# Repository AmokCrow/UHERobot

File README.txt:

This repo is for the Under House Explorer robot project.

Contents:
RobotControlBoard - Code for the MCU on the robot's PCB.
RobotControlDaemon - an FCGI server process. Mediates between the web UI and the control board serial port.
StaticWebContent - The web UI.

Library dependencies:
libpthreads-dev (may be called libevent-pthreads in your distro now)
libfcgi-dev (basic FastCGI interface, get c++ ver if separate)
libpthreads-dev (needed for fcgi's threading)
libcgicc-dev (does the cgi inputs parsing)
spawn-fcgi (a lighttdp spin-off, a magic tool for spawning and un-parenting an fgci process with the right pipe. Don't ask me how it does it.)

Usage:
1. Install the cross-compilation toolchain for your Linux board. (You don't want to compile on a low-power single-board computer, trust me.)
  - For the Arietta board, see acmesystems.it . They made it and provide fairly good instructions for the toolchain.
  - For Raspberry Pi... google "cross-compile Qt for Raspberry Pi".
2. Boot your Linux board. The one that you're going to use as the robot's brains.
3. On your Linux board, install the above libraries, plus Nginx server.
4. Uninstall Apache, unless you know better and/or actually use Apache for something. If it's installed in the first place. Arietta came with Apache installed.
5. Shut down your Linux board. Take out the memory card. Use the "dd" command to copy the card contents into an image on your hard drive.

For Arietta:
6. Mount the larger partition in the image to /mnt/ariettaroot
  - You can get the partitions in the image with the command "fdisk -l <image-file-name>"
  - You then mount with "mount -o loop,offset=<filesystem-offset-in-bytes> <image-file-name> /mnt/ariettaroot
  - You can mount elsewhere, but then you'll have to fix the path to the root filesystem in arietta.cmake
7. Make a directory named "build-daemon". Navigate in it.
8. Copy the arietta.cmake file into this directory.
9. Call cmake with "cmake -DCMAKE_TOOLCHAIN_FILE=arietta.cmake ../RobotControlDaemon"
  - If it complains about not finding referenced items, it means that the Linux board image is missing some of the dependency libraries. Or is not mounted correctly.
10. Call "make"

For Raspberry Pi:
6. Cross-compile Qt. (I had this done. I write what I know.)
7. Install Qt on the Raspberry Pi image.
8. Notice that the qmake executable is actually still built for your PC even though the rest of it is cross-compiled.
9. Navigate to the folder RobotControlDaemon
10. Call the cross-compile qmake
11. Call "make"

Common for both:
12. Copy the image back to the memory card, insert to your Linux board and boot it up.
13. Copy the cross-compiled executable to your board.

For Arietta:
14. Using the online tools at acmesystems.it, make a pin configuration file that will give you a UART.
  - Get the UART on pins that match the custom PCB if mounting it directly on top.
15. Download the configuration file to the Arietta board's boot partition.
16. Replace the previous configuration file there.
17. Reboot the board for the new configuration to take effect.

For Raspberry Pi:
14. Disable the shell in the serial port.
  - On newer images, this is one of the first-bot configuration options.
  - For older images, follow Adafruit's instructions on the subject.

Common for both:
18. Copy the scripts in daemon_build_scripts/target_run_scripts to the Linux board, to folder /home/pi/RCD
19. Copy the folder StaticWebContent to the Linux board to /home/pi/RCD/StaticWebContent
20. Copy the cross-compiled executable to /home/pi/RDC/bin
21. Make /home/pi/RCD/install_config.sh executable and execute it. This should copy the nginx config in the right place.
22. Make similarly executable and execute the install_daemon.sh script. This should get the cross-compiled executable to be handled as a daemon.
23. Check that the UART port name in start_daemon.sh is correct.
24. Make start_daemon.sh and kill_daemon.sh executable if they are not already.
25. Reboot the Linux board.
26. Done. Finished. ...Profit?
  - The Linux board should have the nginx server running and serving the robot's UI.
  - For an easier life, consider setting a static address for the robot. See /etc/networking/interfaces.conf and google "Linux interfaces static address".

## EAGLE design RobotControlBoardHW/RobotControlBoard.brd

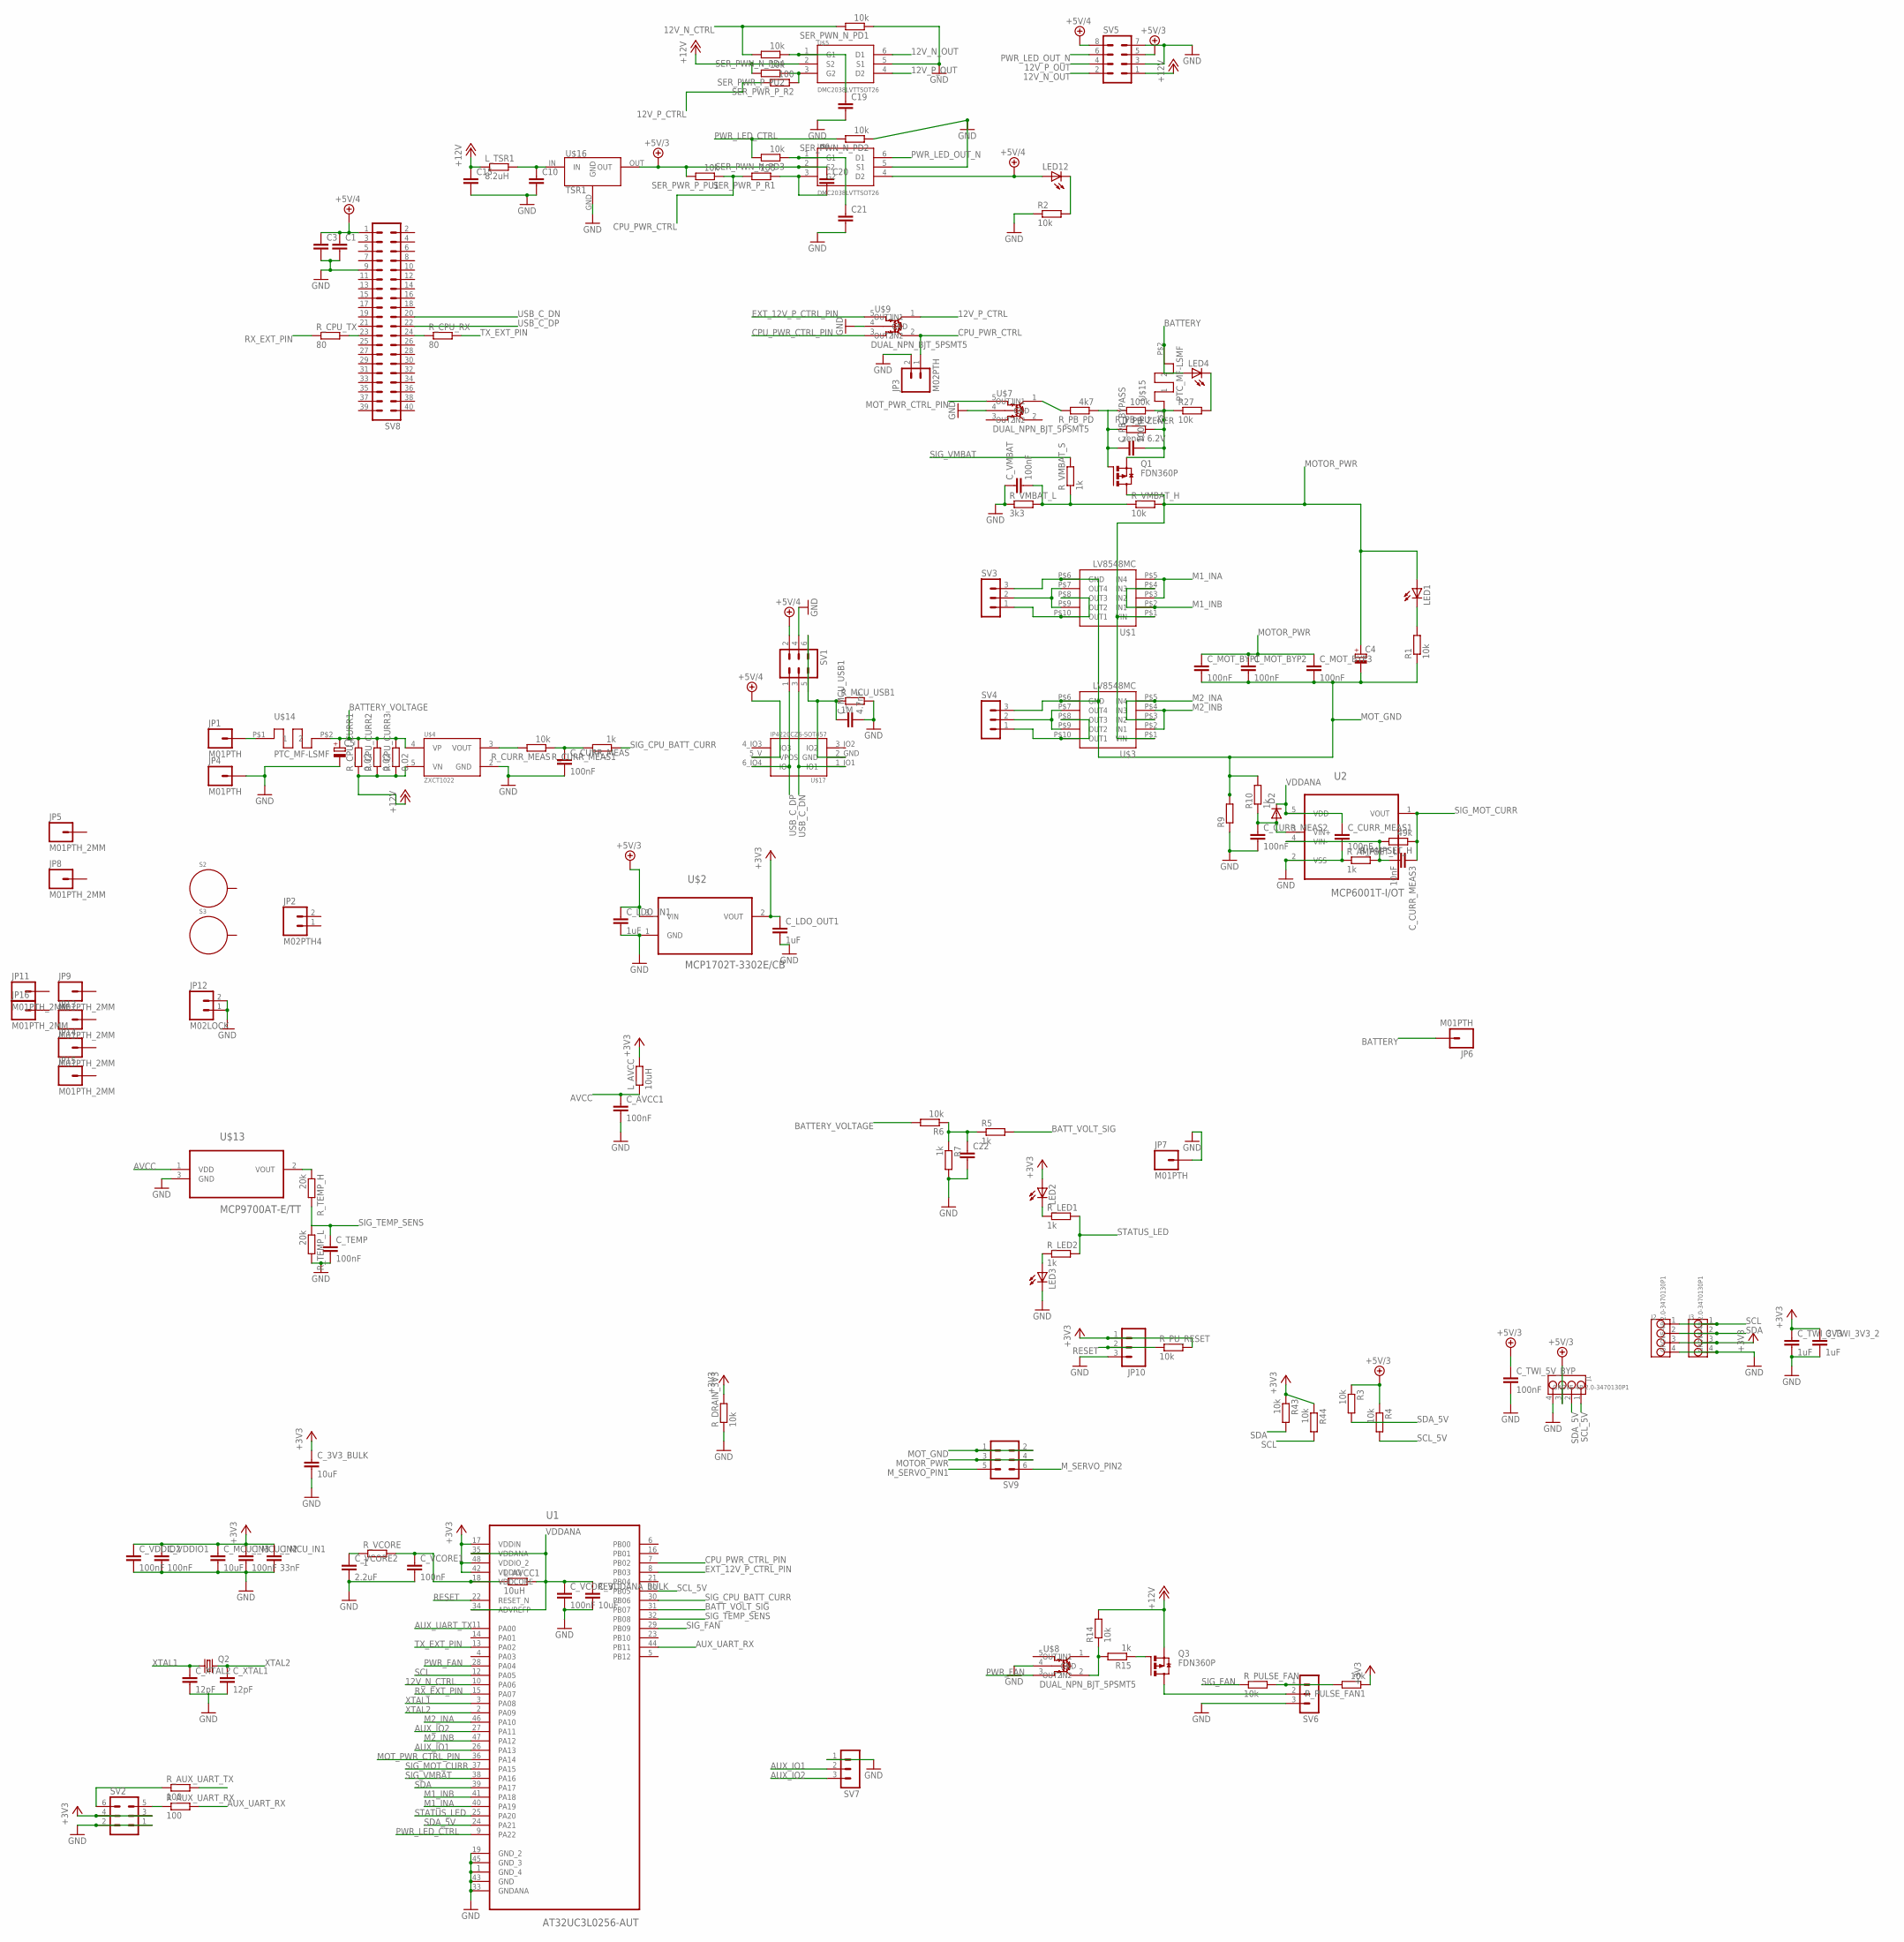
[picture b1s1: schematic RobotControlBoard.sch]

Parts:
C1, C3: C-EUC1210K; C1210K
C4: CPOL-EUE3.5-8; E3,5-8
C5: CPOL-EUE2.5-6; E2,5-6
C10, C15: C-EUC0805; C0805
C19, C20, C21, C22: C-EUC0603K; C0603K
C_3V3_BULK: 10uF; C1206
C_AVCC1: 100nF; C0603
C_CURR_MEAS, C_CURR_MEAS1, C_CURR_MEAS2: 100nF; C0603K
C_CURR_MEAS3: 10nF; C0603K
C_LDO_IN1: 1uF; C0805
C_LDO_OUT1: 1uF; C0805
C_MCU_IN1: 33nF; C0603K
C_MCU_IN2: 100nF; C0603K
C_MCU_IN3: 10uF; C0805
C_MCU_USB1: 4.7nF; C0603
C_MOT_BYP1, C_MOT_BYP2, C_MOT_BYP3: 100nF; C0603K
C_PB_BYPASS: 100nF; C0603K
C_TEMP: 100nF; C0603
C_TWI_3V3, C_TWI_3V3_2: 1uF; C0805K
C_TWI_5V_BYP: 100nF; C0603K
C_VCORE1, C_VCORE3: 100nF; C0603K
C_VCORE2: 2.2uF; C0805
C_VDDANA_BULK: 10uF; C0805
C_VDDIO1, C_VDDIO2: 100nF; C0603K
C_VMBAT: 100nF; C0603K
C_XTAL1, C_XTAL2: 12pF; C0603K
D2: DIODE-SOD323-W; SOD323-W
D_PB_ZENER: zener 6.2V; R0805W
J1, J2, J3: GROVE-4P-2.0-3470130P1; 4P-2.0
JP1, JP4, JP6, JP7: M01PTH; 1X01
JP2: M02PTH4; 1X02_XTRA_BIG
JP3: M02PTH; 1X02
JP5, JP8, JP9, JP11, JP13, JP14, JP15, JP16: M01PTH_2MM; 1X01_2MM
JP10: M03PTH; 1X03
JP12: M02LOCK; 1X02_LOCK
LED1, LED2, LED3, LED4, LED12: LEDSML0603; SML0603
L_AVCC: 10uH; R0603
L_AVCC1: 10uH; R0805
L_TSR1: 8.2uH; M0805
Q1, Q3: FDN360P; SUPER-SOT3
Q2: CRYSTALHC49S; HC49/S
R1, R2, R3, R4, R6, R14, R27, R43, R44: 10k; R0603
R5, R7, R10, R15: 1k; R0603
R9: R-EU_M1206; M1206
R_AMPSET_H: 49k; R0603
R_AMPSET_L: 1k; R0603
R_AUX_UART_RX: 100; R0603
R_AUX_UART_TX: 100; R0603
R_CPU_CURR1, R_CPU_CURR2, R_CPU_CURR3: 0.02; R0805
R_CPU_RX: 80; R0603
R_CPU_TX: 80; R0603
R_CURR_MEAS: 10k; R0603
R_CURR_MEAS1: 1k; R0603
R_DRAIN_3V3: 10k; R0603
R_LED1, R_LED2: 1k; R0603
R_MCU_USB1: 1M; R0603
R_PB_PD: 4k7; R0603
R_PB_PU: 100k; R0603
R_PULSE_FAN, R_PULSE_FAN1: 10k; R0603
R_PU_RESET: 10k; R0603
R_TEMP_H: 20k; R0603
R_TEMP_L: 20k; R0603
R_VCORE: 1; R0603
R_VMBAT_H: 10k; R0603
R_VMBAT_L: 3k3; R0603
R_VMBAT_S: 1k; R0603
S2, S3: STANDOFF_ELECTRICAL; STANDOFF-ELECTRICAL
SER_PWN_N_PD1, SER_PWN_N_PD2, SER_PWN_N_PD3, SER_PWN_N_PD4: 10k; R0603
SER_PWR_P_PU1, SER_PWR_P_PU2: 10k; R0603
SER_PWR_P_R1, SER_PWR_P_R2: 100; R0603
SV1, SV2, SV9: MA03-2
SV3, SV4, SV6, SV7: MA03-1
SV5: MA04-2
SV8: MA20-2
U1: AT32UC3L0256-AUT; QFP50P900X900X120-48N
U2: MCP6001T-I/OT; SOT95P270X145-5N
U$1, U$3: LV8548MC; SOIC10
U$2: MCP1702T-3302E/CB; SOT95P255X145-3N
U$4: ZXCT1022; SOT23-5
U$5, U$6: DMC2038LVTTSOT26; TSOT26
U$7, U$8, U$9: DUAL_NPN_BJT_5PSMT5; SC-74A
U$13: MCP9700AT-E/TT; SOT95P237X112-3N
U$14, U$15: PTC_MF-LSMF; PTC_FUSE_BOURNS
U$16: TSR1; TSR-1
U$17: IP4220CZ6-SOT457; SOT457_NXP_ESD

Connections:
12V_N_CTRL: SER_PWN_N_PD1.2, SER_PWN_N_PD4.2, U1.10 (PA06)
12V_N_OUT: SV5.2, U$5.6 (D1)
12V_P_CTRL: SER_PWR_P_R2.2, U$9.1 (OUT1)
12V_P_OUT: SV5.4, U$5.4 (D2)
+3V3: C_3V3_BULK.1, C_LDO_OUT1.1, C_MCU_IN1.1, C_MCU_IN2.1, C_MCU_IN3.1, C_TWI_3V3.1, C_TWI_3V3_2.1, C_VDDIO1.1, C_VDDIO2.1, J2.3, J3.3, JP10.1, LED2.A, L_AVCC.2, R43.1, R44.1, R_DRAIN_3V3.2, R_PULSE_FAN1.1, R_PU_RESET.2, SV2.3, SV2.4, U1.17 (VDDIN), U1.42 (VDDIO), U1.48 (VDDIO_2), U$2.2 (VOUT)
+5V/3: C20.1, C_LDO_IN1.1, C_TWI_5V_BYP.1, J1.3, R3.1, R4.1, SER_PWR_P_PU1.2, SV5.5, U$2.3 (VIN), U$6.2 (S2), U$16.OUT
+5V/4: C1.1, C3.1, LED12.A, SV1.2, SV5.8, SV8.1, U$6.4 (D2), U$17.5_V (VPOS)
+12V: C15.1, L_TSR1.1, Q3.2 (S), R14.2, R_CPU_CURR1.1, R_CPU_CURR2.1, R_CPU_CURR3.1, SER_PWR_P_PU2.2, SV5.1, U$4.5 (VN), U$5.2 (S2)
AUX_IO1: SV7.2, U1.26 (PA13)
AUX_IO2: SV7.3, U1.27 (PA11)
AUX_UART_RX: R_AUX_UART_RX.2, U1.44 (PB11)
AUX_UART_TX: R_AUX_UART_TX.2, U1.11 (PA00)
AVCC: C_AVCC1.1, L_AVCC.1, U$13.1 (VDD)
BATTERY: JP6.1, LED4.A, U$15.P$2 (2)
BATTERY_VOLTAGE: C5.+, R6.2, R_CPU_CURR1.2, R_CPU_CURR2.2, R_CPU_CURR3.2, U$4.4 (VP), U$14.P$2 (2)
BATT_VOLT_SIG: R5.2, U1.31 (PB07)
BATT_VOLT_SIG_N: C22.1, R5.1, R6.1, R7.1
CPU_PWR_CTRL: JP3.1, SER_PWR_P_PU1.1, SER_PWR_P_R1.2, U$9.2 (OUT2)
CPU_PWR_CTRL_PIN: U1.7 (PB02), U$9.3 (IN2)
EXT_12V_P_CTRL_PIN: U1.8 (PB03), U$9.5 (IN1)
GND: C1.2, C3.2, C5.-, C10.2, C15.2, C19.2, C21.2, C22.2, C_3V3_BULK.2, C_AVCC1.2, C_CURR_MEAS.2, C_CURR_MEAS1.2, C_CURR_MEAS2.2, C_LDO_IN1.2, C_LDO_OUT1.2, C_MCU_IN1.2, C_MCU_IN2.2, C_MCU_IN3.2, C_MCU_USB1.2, C_TEMP.2, C_TWI_3V3.2, C_TWI_3V3_2.2, C_TWI_5V_BYP.2, C_VCORE1.2, C_VCORE2.2, C_VCORE3.2, C_VDDANA_BULK.2, C_VDDIO1.2, C_VDDIO2.2, C_VMBAT.1, C_XTAL1.2, C_XTAL2.2, J1.4, J2.4, J3.4, JP3.2, JP4.1, JP7.1, JP10.3, JP12.1, JP12.2, LED3.C, R2.1, R7.2, R9.1, R_AMPSET_L.1, R_DRAIN_3V3.1, R_MCU_USB1.2, R_TEMP_L.2, R_VMBAT_L.1, SER_PWN_N_PD1.1, SER_PWN_N_PD2.1, SV1.4, SV2.1, SV2.2, SV5.3, SV5.7, SV6.3, SV7.1, SV8.9, U1.1 (GND_4), U1.19 (GND_2), U1.33 (GNDANA), U1.43 (GND), U1.45 (GND_3), U2.2 (VSS), U$2.1 (GND), U$4.2 (GND), U$5.5 (S1), U$6.5 (S1), U$7.4 (GND), U$8.4 (GND), U$9.4 (GND), U$13.3 (GND), U$16.GND
M1_INA: U1.40 (PA19), U$1.P$3 (IN2), U$1.P$5 (IN4)
M1_INB: U1.41 (PA18), U$1.P$2 (IN1), U$1.P$4 (IN3)
M2_INA: U1.46 (PA10), U$3.P$3 (IN2), U$3.P$5 (IN4)
M2_INB: U1.47 (PA12), U$3.P$2 (IN1), U$3.P$4 (IN3)
MOTOR_PWR: C4.+, C_MOT_BYP1.1, C_MOT_BYP2.1, C_MOT_BYP3.1, LED1.A, Q1.3 (D), R_VMBAT_H.2, SV9.3, SV9.4, U$1.P$1 (VIN), U$3.P$1 (VIN)
MOT_GND: C4.-, C_MOT_BYP1.2, C_MOT_BYP2.2, C_MOT_BYP3.2, R1.1, R9.2, R10.2, SV3.3, SV4.3, SV9.1, SV9.2, U$1.P$6 (GND), U$3.P$6 (GND)
MOT_PWR_CTRL_PIN: U1.36 (PA14), U$7.5 (IN1)
M_SERVO_PIN1: SV9.5
M_SERVO_PIN2: SV9.6
unnamed: R_AUX_UART_RX.1, SV2.5
unnamed: LED3.A, R_LED2.1
unnamed: LED2.C, R_LED1.1
unnamed: R_CURR_MEAS.2, U$4.3 (VOUT)
unnamed: C_VMBAT.2, R_VMBAT_H.1, R_VMBAT_L.2, R_VMBAT_S.1
unnamed: JP1.1, U$14.P$1 (1)
unnamed: C_VCORE2.1, R_VCORE.1
unnamed: C20.2, SER_PWR_P_R1.1, U$6.3 (G2)
unnamed: SV3.1, U$1.P$8 (OUT3), U$1.P$10 (OUT1)
unnamed: C19.1, SER_PWN_N_PD4.1, U$5.1 (G1)
unnamed: SV3.2, U$1.P$7 (OUT4), U$1.P$9 (OUT2)
unnamed: C_PB_BYPASS.2, D_PB_ZENER.2, Q1.2 (S), R27.1, R_PB_PU.1, U$15.P$1 (1)
unnamed: SER_PWR_P_PU2.1, SER_PWR_P_R2.1, U$5.3 (G2)
unnamed: R_AUX_UART_TX.1, SV2.6
unnamed: C_PB_BYPASS.1, D_PB_ZENER.1, Q1.1 (G), R_PB_PD.1, R_PB_PU.2
unnamed: R_TEMP_H.1, U$13.2 (VOUT)
unnamed: R_PB_PD.2, U$7.1 (OUT1)
unnamed: LED1.C, R1.2
unnamed: SV4.2, U$3.P$7 (OUT4), U$3.P$9 (OUT2)
unnamed: SV4.1, U$3.P$8 (OUT3), U$3.P$10 (OUT1)
unnamed: C_VCORE1.1, L_AVCC1.1, R_VCORE.2, U1.18 (VDDCORE)
unnamed: C10.1, L_TSR1.2, U$16.IN
unnamed: C_CURR_MEAS2.1, D2.A, R10.1, U2.3 (VIN+)
unnamed: C_CURR_MEAS3.2, R_AMPSET_H.2, R_AMPSET_L.2, U2.4 (VIN-)
unnamed: LED4.C, R27.2
unnamed: R_CPU_RX.1, SV8.24
unnamed: R_CPU_TX.2, SV8.23
unnamed: C_MCU_USB1.1, R_MCU_USB1.1, SV1.5, SV1.6, U$17.2_GND (GND)
unnamed: Q3.1 (G), R15.1
unnamed: R14.1, R15.2, U$8.2 (OUT2)
unnamed: Q3.3 (D), SV6.2
unnamed: R_PULSE_FAN.2, R_PULSE_FAN1.2, SV6.1
unnamed: C21.1, SER_PWN_N_PD3.1, U$6.1 (G1)
unnamed: LED12.C, R2.2
PWR_FAN: U1.28 (PA04), U$8.3 (IN2)
PWR_LED_CTRL: SER_PWN_N_PD2.2, SER_PWN_N_PD3.2, U1.9 (PA22)
PWR_LED_OUT_N: SV5.6, U$6.6 (D1)
RESET: JP10.2, R_PU_RESET.1, U1.22 (RESET_N)
RX_EXT_PIN: R_CPU_TX.1, U1.15 (PA07)
SCL: J2.1, J3.1, R44.2, U1.12 (PA05)
SCL_5V: J1.1, R4.2, U1.20 (PB05)
SDA: J2.2, J3.2, R43.2, U1.39 (PA17)
SDA_5V: J1.2, R3.2, U1.24 (PA21)
SIG_CPU_BATT_CURR: R_CURR_MEAS1.1, U1.30 (PB06)
SIG_CPU_BATT_CURRENT_N: C_CURR_MEAS.1, R_CURR_MEAS.1, R_CURR_MEAS1.2
SIG_FAN: R_PULSE_FAN.1, U1.29 (PB09)
SIG_MOT_CURR: C_CURR_MEAS3.1, R_AMPSET_H.1, U1.37 (PA15), U2.1 (VOUT)
SIG_TEMP_SENS: C_TEMP.1, R_TEMP_H.2, R_TEMP_L.1, U1.32 (PB08)
SIG_VMBAT: R_VMBAT_S.2, U1.38 (PA16)
STATUS_LED: R_LED1.2, R_LED2.2, U1.25 (PA20)
TX_EXT_PIN: R_CPU_RX.2, U1.13 (PA02)
USB_C_DN: SV1.3, SV8.20, U$17.1_IO1 (IO1)
USB_C_DP: SV1.1, SV8.22, U$17.6_IO4 (IO4)
VDDANA: C_CURR_MEAS1.1, C_VCORE3.1, C_VDDANA_BULK.1, D2.C, L_AVCC1.2, U1.34 (ADVREFP), U1.35 (VDDANA), U2.5 (VDD)
XTAL1: C_XTAL2.1, Q2.1, U1.3 (PA08)
XTAL2: C_XTAL1.1, Q2.2, U1.2 (PA09)

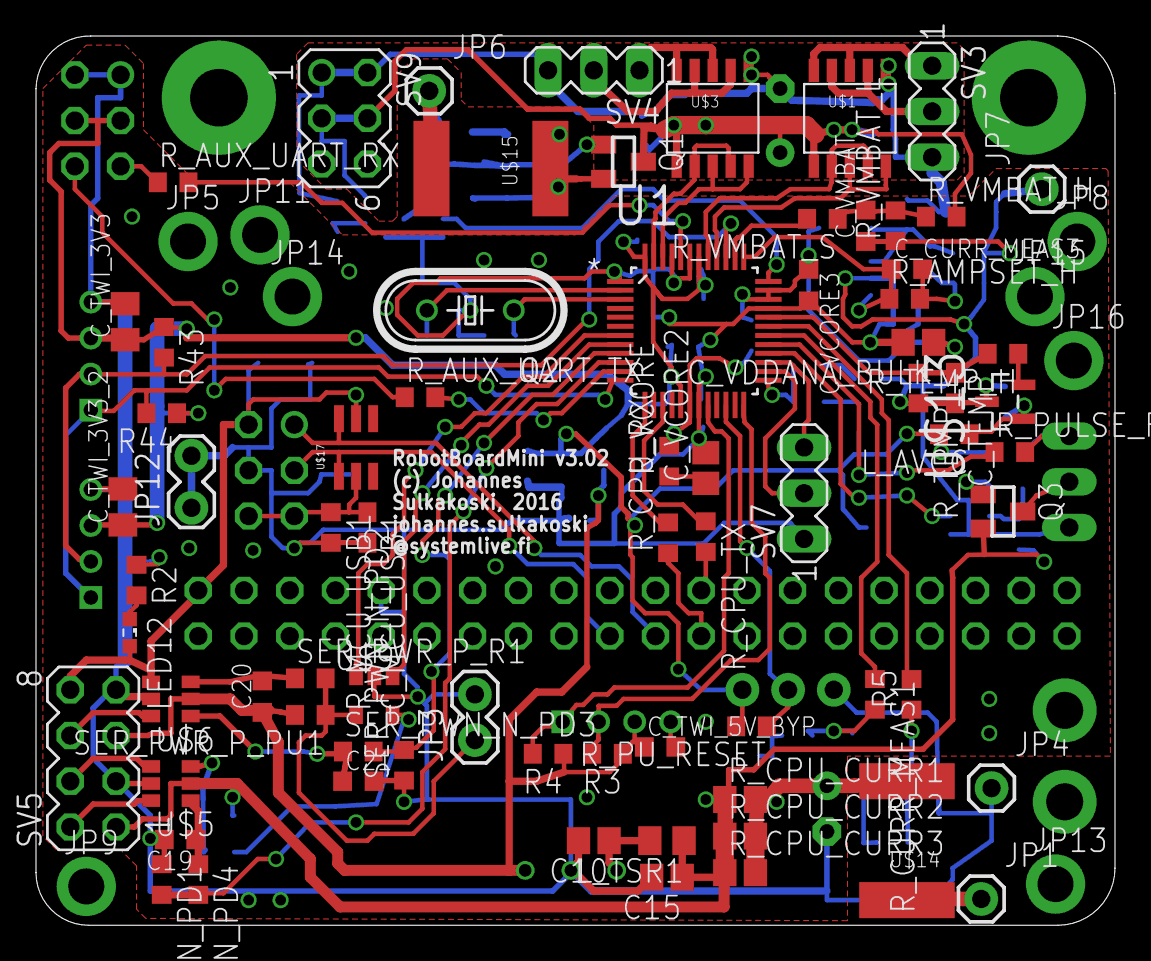
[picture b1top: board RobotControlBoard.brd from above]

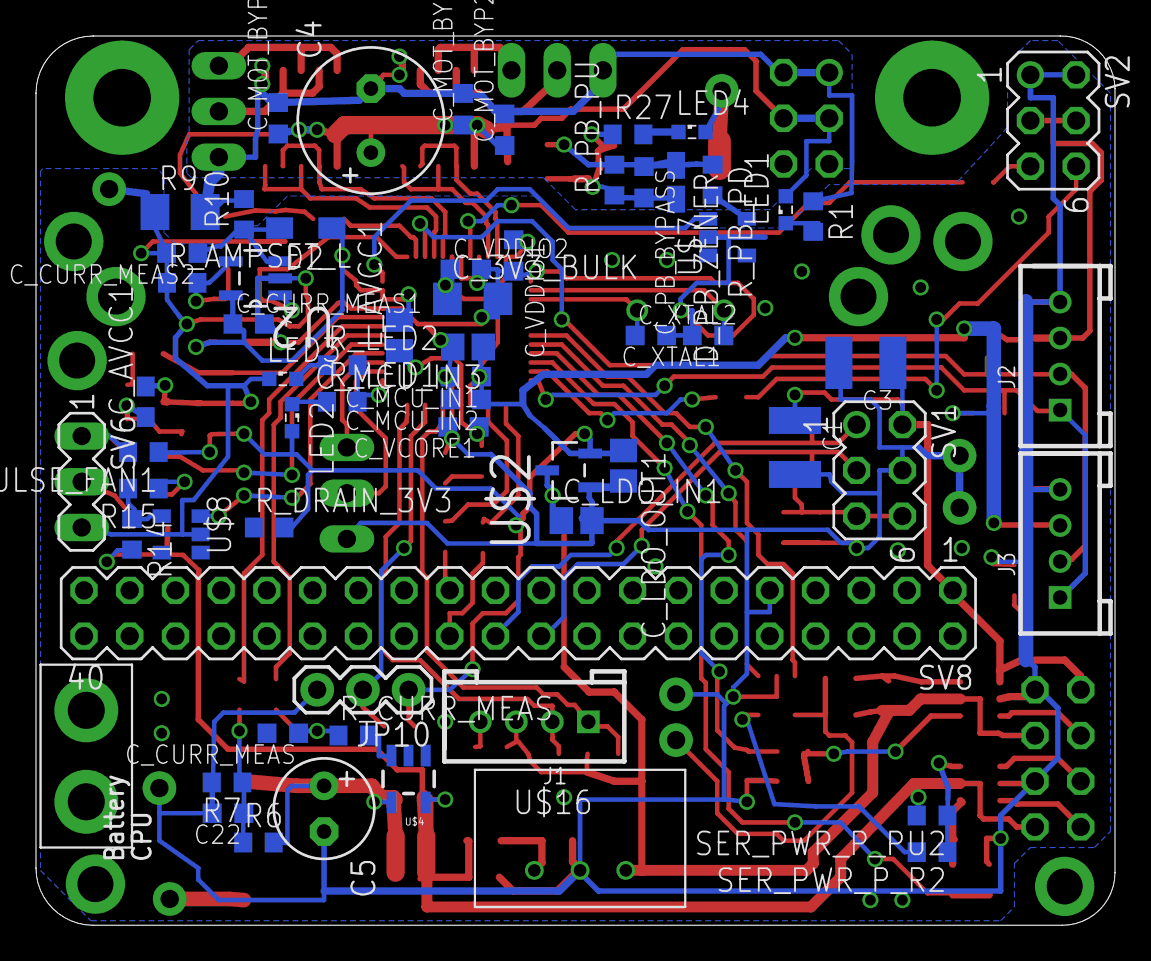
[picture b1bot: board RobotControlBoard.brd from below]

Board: 4 copper layers, 59.9 x 49.4 mm, 146 parts (64 on the bottom side), 84 nets.

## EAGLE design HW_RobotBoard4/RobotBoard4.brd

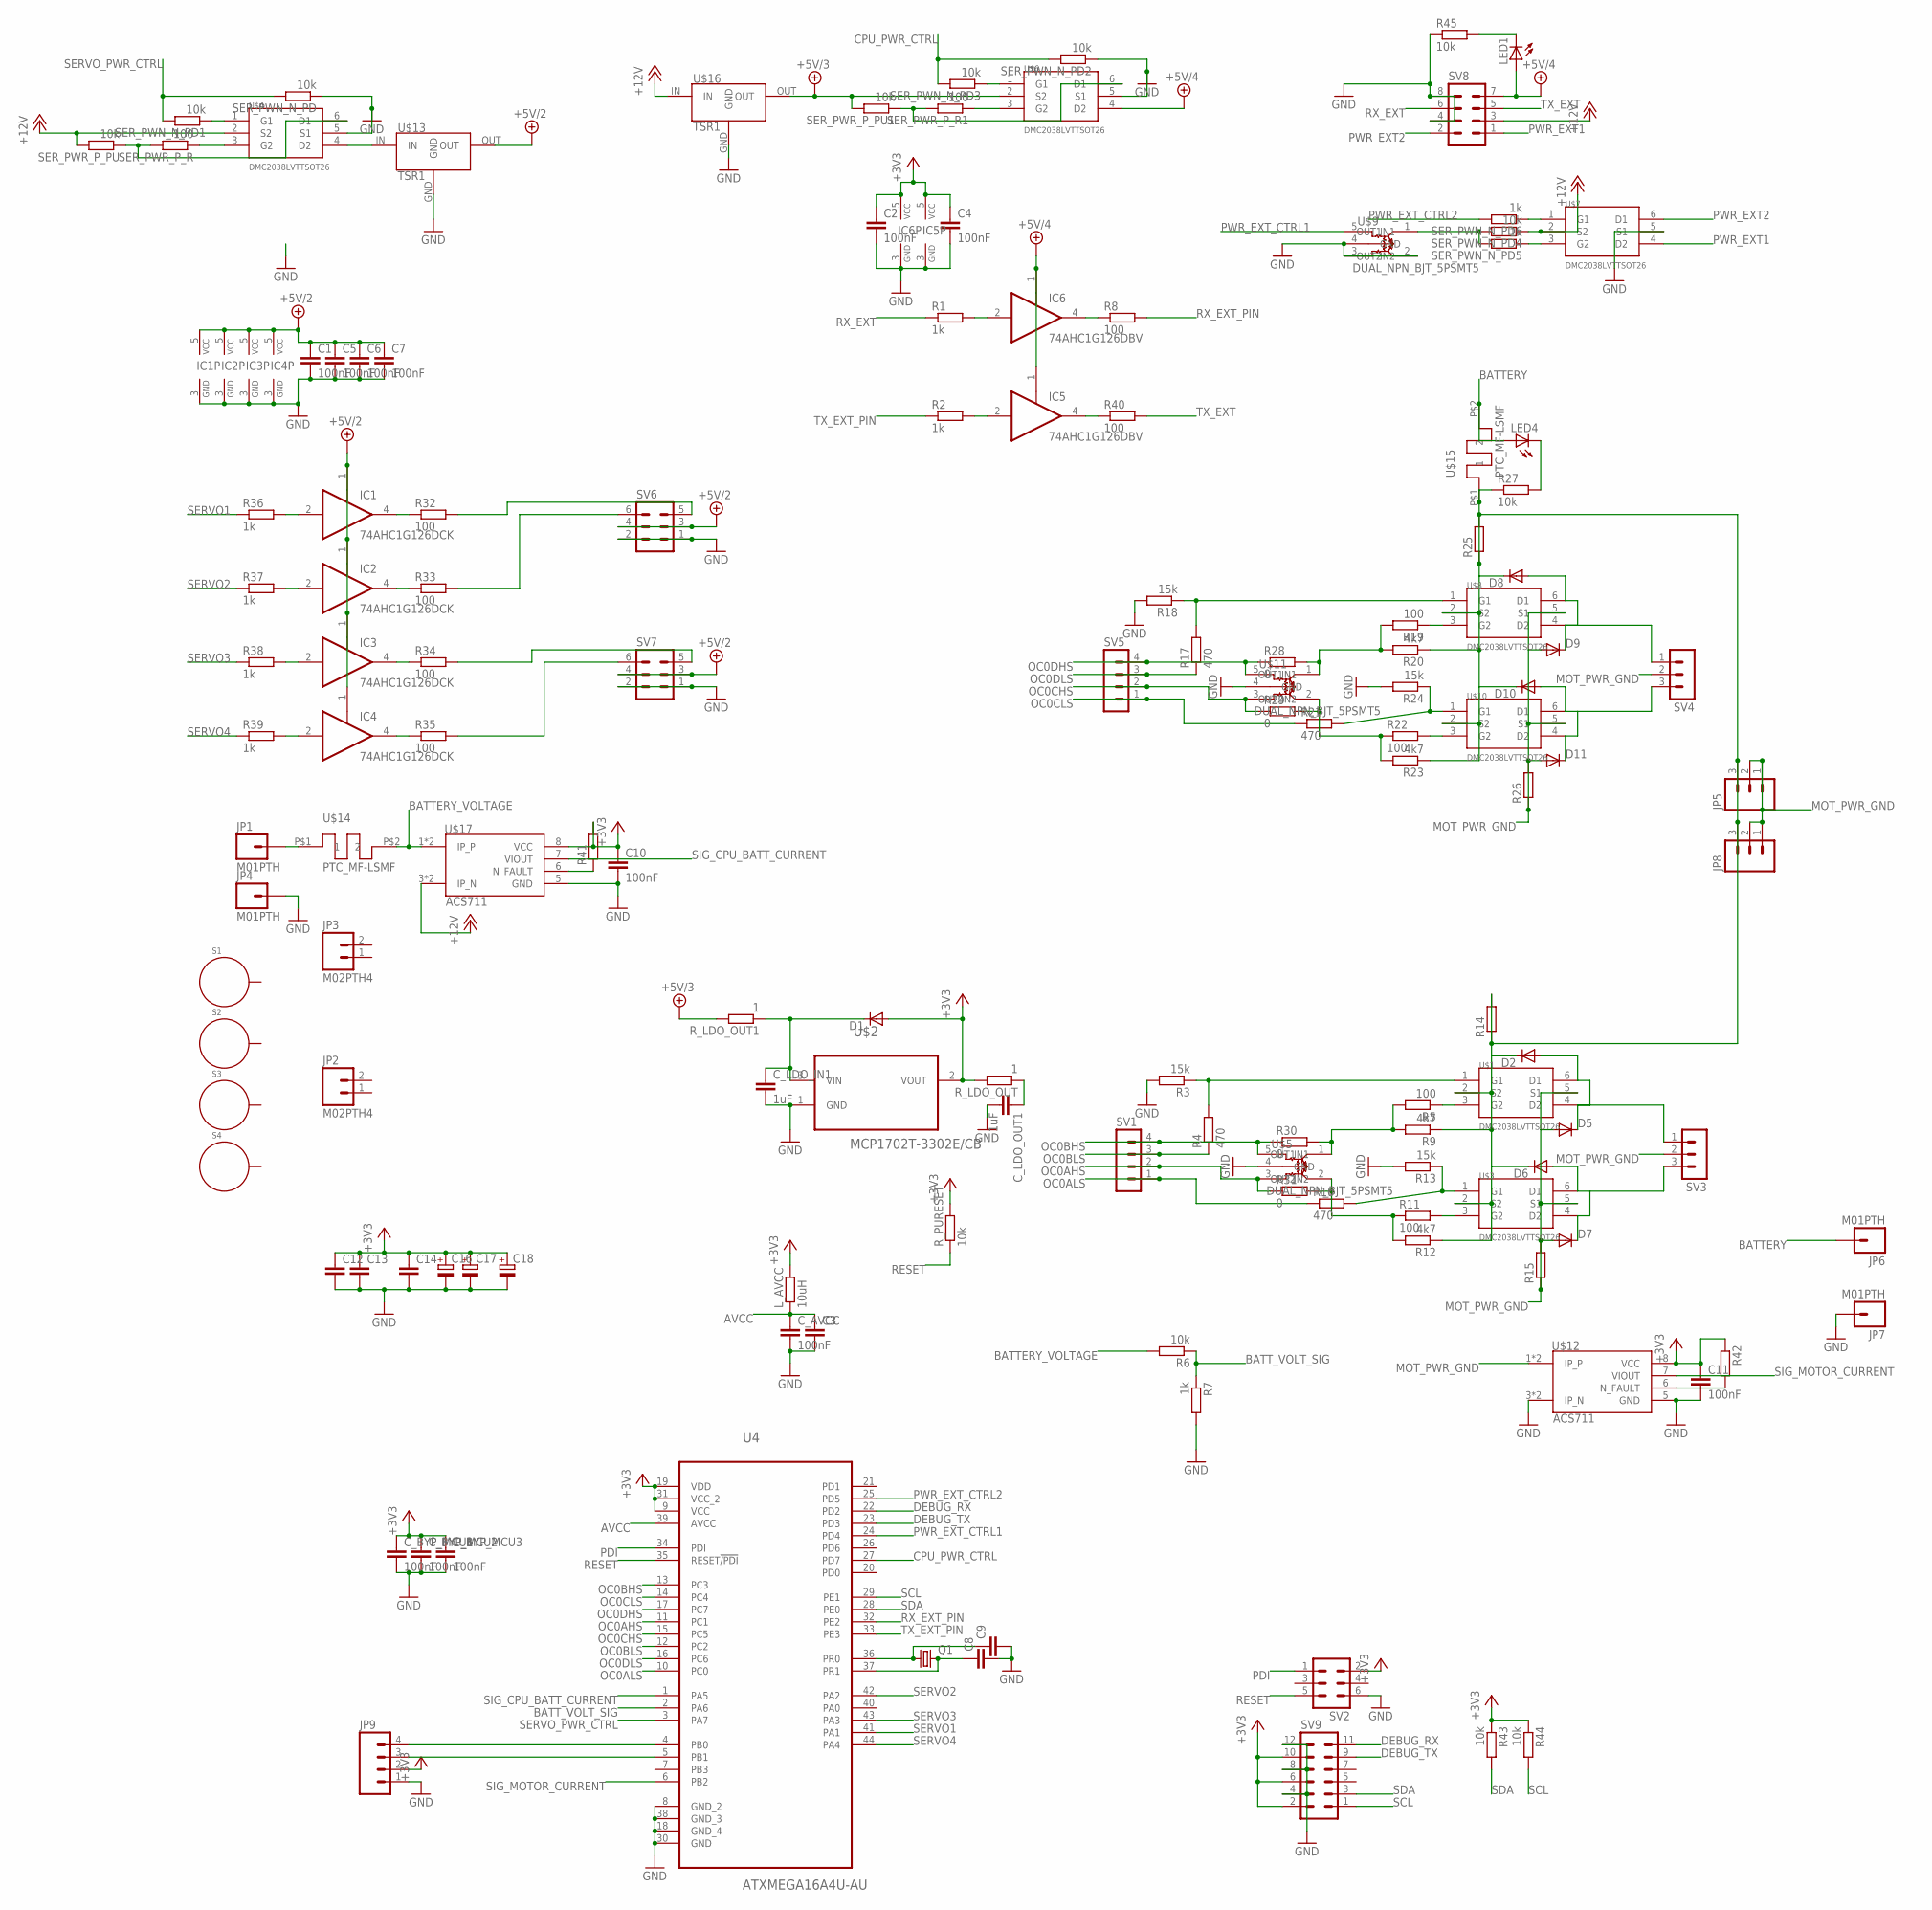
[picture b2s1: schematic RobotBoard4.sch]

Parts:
C1, C5, C6, C7: 100nF; C0603
C2, C4, C10, C11: 100nF; C0603K
C3: C-EUC1206K; C1206K
C8, C9: C-EUC0603K; C0603K
C12, C13: C-EUC0805K; C0805K
C14: C-EUC1210; C1210
C16, C17: CPOL-EUE2.5-6; E2,5-6
C18: CPOL-EU153CLV-0505; 153CLV-0505
C_AVCC: 100nF; C0603
C_BYP_MCU1, C_BYP_MCU2, C_BYP_MCU3: 100nF; C0603
C_LDO_IN1: 1uF; C0805
C_LDO_OUT1: 1uF; C0805
D1: DIODE-SOD523; SOD523
D2, D5, D6, D7, D8, D9, D10, D11: DIODE-SOD123; SOD123
IC1, IC2, IC3, IC4: 74AHC1G126DCK; SC70-5
IC5, IC6: 74AHC1G126DBV; SOT23-5
JP1, JP4, JP6, JP7: M01PTH; 1X01
JP2, JP3: M02PTH4; 1X02_XTRA_BIG
JP5, JP8: M03PTH; 1X03
JP9: M04PTH; 1X04
LED1, LED4: LEDSML0603; SML0603
L_AVCC: 10uH; R0805
Q1: CRYSTALHC49S; HC49/S
R1, R2, R7, R36, R37, R38, R39: 1k; R0603
R3, R13, R18, R24: 15k; R0603
R4, R10, R17, R21: 470; R0603
R5, R8, R11, R19, R22, R32, R33, R34, R35, R40: 100; R0603
R6, R27, R43, R44, R45: 10k; R0603
R9, R12, R20, R23: 4k7; R0603
R14, R15, R25, R26: R-EU_0204/5; 0204/5
R28, R29, R30, R31: 0; R0603
R41, R42: R-EU_R0603; R0603
R_LDO_OUT, R_LDO_OUT1: 1; R0603
R_PURESET: 10k; R0603
S1, S2, S3, S4: STANDOFF_ELECTRICAL; STANDOFF-ELECTRICAL
SER_PWN_N_PD, SER_PWN_N_PD1, SER_PWN_N_PD2, SER_PWN_N_PD3, SER_PWN_N_PD4: 10k; R0603
SER_PWN_N_PD5, SER_PWN_N_PD6: 1k; R0603
SER_PWR_P_PU, SER_PWR_P_PU1: 10k; R0603
SER_PWR_P_R, SER_PWR_P_R1: 100; R0603
SV1, SV5: MA04-1
SV2, SV6, SV7: MA03-2
SV3, SV4: MA03-1
SV8: MA04-2
SV9: MA06-2
U4: ATXMEGA16A4U-AU; QFP80P1200X1200X120-44N
U$1, U$3, U$4, U$6, U$7, U$8, U$10: DMC2038LVTTSOT26; TSOT26
U$2: MCP1702T-3302E/CB; SOT95P255X145-3N
U$5, U$9, U$11: DUAL_NPN_BJT_5PSMT5; SC-74A
U$12, U$17: ACS711; SO08
U$13, U$16: TSR1; TSR-1
U$14, U$15: PTC_MF-LSMF; PTC_FUSE_BOURNS

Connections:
+3V3: C2.1, C4.1, C10.1, C11.1, C12.1, C13.1, C14.1, C16.+, C17.+, C18.+, C_BYP_MCU1.1, C_BYP_MCU2.1, C_BYP_MCU3.1, D1.A, IC5.5 (VCC), IC6.5 (VCC), JP9.2, L_AVCC.2, R41.2, R42.1, R43.1, R44.1, R_LDO_OUT.2, R_PURESET.2, SV2.2, SV9.2, SV9.6, SV9.10, U4.9 (VCC), U4.19 (VDD), U4.31 (VCC_2), U$2.2 (VOUT), U$12.8 (VCC), U$17.8 (VCC)
+5V/2: C1.1, C5.1, C6.1, C7.1, IC1.1 (OE), IC1.5 (VCC), IC2.1 (OE), IC2.5 (VCC), IC3.1 (OE), IC3.5 (VCC), IC4.1 (OE), IC4.5 (VCC), SV6.3, SV6.4, SV7.3, SV7.4, U$13.OUT
+5V/3: R_LDO_OUT1.2, SER_PWR_P_PU1.2, U$6.2 (S2), U$16.OUT
+5V/4: IC5.1 (OE), IC6.1 (OE), LED1.A, SV8.7, U$6.4 (D2)
+12V: SER_PWN_N_PD4.1, SER_PWR_P_PU.2, SV8.3, U$4.2 (S2), U$7.2 (S2), U$16.IN, U$17.3 (IP_N), U$17.4 (IP_N)
AVCC: C3.1, C_AVCC.1, L_AVCC.1, U4.39 (AVCC)
BATTERY: JP6.1, LED4.A, U$15.P$2 (2)
BATTERY_VOLTAGE: R6.2, U$14.P$2 (2), U$17.1 (IP_P), U$17.2 (IP_P)
BATT_VOLT_SIG: R6.1, R7.1, U4.2 (PA6)
CPU_PWR_CTRL: SER_PWN_N_PD2.2, SER_PWN_N_PD3.2, U4.27 (PD7)
DEBUG_RX: SV9.11, U4.22 (PD2)
DEBUG_TX: SV9.9, U4.23 (PD3)
GND: C1.2, C2.2, C3.2, C4.2, C5.2, C6.2, C7.2, C8.2, C9.2, C10.2, C11.2, C12.2, C13.2, C14.2, C16.-, C17.-, C18.-, C_AVCC.2, C_BYP_MCU1.2, C_BYP_MCU2.2, C_BYP_MCU3.2, C_LDO_IN1.2, C_LDO_OUT1.2, IC1.3 (GND), IC2.3 (GND), IC3.3 (GND), IC4.3 (GND), IC5.3 (GND), IC6.3 (GND), JP4.1, JP7.1, JP9.1, R3.2, R7.2, R13.2, R18.2, R24.2, R45.1, SER_PWN_N_PD.1, SER_PWN_N_PD2.1, SV2.6, SV6.1, SV6.2, SV7.1, SV7.2, SV8.4, SV8.8, SV9.4, SV9.8, SV9.12, U4.8 (GND_2), U4.18 (GND_4), U4.30 (GND), U4.38 (GND_3), U$2.1 (GND), U$4.5 (S1), U$5.4 (GND), U$6.5 (S1), U$7.5 (S1), U$9.2 (OUT2), U$9.3 (IN2), U$9.4 (GND), U$11.4 (GND), U$12.3 (IP_N), U$12.4 (IP_N), U$12.5 (GND), U$13.GND, U$16.GND, U$17.5 (GND)
MOT_PWR_GND: D5.A, D7.A, D9.A, D11.A, JP5.1, JP5.2, JP8.1, JP8.2, R15.1, R15.2, R26.1, R26.2, SV3.2, SV4.2, U$1.5 (S1), U$3.5 (S1), U$8.5 (S1), U$10.5 (S1), U$12.1 (IP_P), U$12.2 (IP_P)
unnamed: R5.2, R9.2, R30.2, U$5.1 (OUT1)
unnamed: SER_PWR_P_PU.1, SER_PWR_P_R.2, U$4.6 (D1)
unnamed: SER_PWR_P_R.1, U$4.3 (G2)
unnamed: C_LDO_OUT1.1, R_LDO_OUT.1
unnamed: JP9.4, U4.4 (PB0)
unnamed: JP1.1, U$14.P$1 (1)
unnamed: SER_PWN_N_PD1.1, U$4.1 (G1)
unnamed: C_LDO_IN1.1, D1.C, R_LDO_OUT1.1, U$2.3 (VIN)
unnamed: SER_PWR_P_PU1.1, SER_PWR_P_R1.2, U$6.6 (D1)
unnamed: SER_PWR_P_R1.1, U$6.3 (G2)
unnamed: R11.1, R12.2, R31.2, U$5.2 (OUT2)
unnamed: R3.1, R4.2, U$1.1 (G1)
unnamed: R5.1, U$1.3 (G2)
unnamed: R10.2, R13.1, U$3.1 (G1)
unnamed: R11.2, U$3.3 (G2)
unnamed: JP9.3, U4.5 (PB1)
unnamed: D2.A, D5.C, SV3.1, U$1.4 (D2), U$1.6 (D1)
unnamed: IC1.4 (O), R32.1
unnamed: D6.A, D7.C, SV3.3, U$3.4 (D2), U$3.6 (D1)
unnamed: R17.2, R18.1, U$8.1 (G1)
unnamed: R19.1, U$8.3 (G2)
unnamed: R19.2, R20.2, R28.2, U$11.1 (OUT1)
unnamed: D2.C, D6.C, D8.C, D10.C, JP5.3, JP8.3, R9.1, R12.1, R14.1, R14.2, R20.1, R23.1, R25.1, R25.2, R27.1, U$1.2 (S2), U$3.2 (S2), U$8.2 (S2), U$10.2 (S2), U$15.P$1 (1)
unnamed: IC6.2 (I), R1.2
unnamed: R22.1, R23.2, R29.2, U$11.2 (OUT2)
unnamed: R21.2, R24.1, U$10.1 (G1)
unnamed: R22.2, U$10.3 (G2)
unnamed: LED4.C, R27.2
unnamed: D8.A, D9.C, SV4.1, U$8.4 (D2), U$8.6 (D1)
unnamed: D10.A, D11.C, SV4.3, U$10.4 (D2), U$10.6 (D1)
unnamed: IC2.4 (O), R33.1
unnamed: IC3.4 (O), R34.1
unnamed: IC4.4 (O), R35.1
unnamed: IC1.2 (I), R36.2
unnamed: IC2.2 (I), R37.2
unnamed: IC3.2 (I), R38.2
unnamed: IC4.2 (I), R39.2
unnamed: R32.2, SV6.5
unnamed: R33.2, SV6.6
unnamed: R34.2, SV7.5
unnamed: R35.2, SV7.6
unnamed: SER_PWN_N_PD3.1, U$6.1 (G1)
unnamed: U$4.4 (D2), U$13.IN
unnamed: C9.1, Q1.1, U4.36 (PR0)
unnamed: C8.1, Q1.2, U4.37 (PR1)
unnamed: IC5.2 (I), R2.2
unnamed: IC5.4 (O), R40.1
unnamed: IC6.4 (O), R8.1
unnamed: R42.2, U$12.6 (N_FAULT)
unnamed: SER_PWN_N_PD5.1, U$7.3 (G2)
unnamed: SER_PWN_N_PD4.2, SER_PWN_N_PD5.2, U$9.1 (OUT1)
unnamed: SER_PWN_N_PD6.1, U$7.1 (G1)
unnamed: LED1.C, R45.2
unnamed: R41.1, U$17.6 (N_FAULT)
OC0AHS: R31.1, SV1.2, U4.11 (PC1), U$5.3 (IN2)
OC0ALS: R10.1, SV1.1, U4.10 (PC0)
OC0BHS: R30.1, SV1.4, U4.13 (PC3), U$5.5 (IN1)
OC0BLS: R4.1, SV1.3, U4.12 (PC2)
OC0CHS: R29.1, SV5.2, U4.15 (PC5), U$11.3 (IN2)
OC0CLS: R21.1, SV5.1, U4.14 (PC4)
OC0DHS: R28.1, SV5.4, U4.17 (PC7), U$11.5 (IN1)
OC0DLS: R17.1, SV5.3, U4.16 (PC6)
PDI: SV2.1, U4.34 (PDI)
PWR_EXT1: SV8.1, U$7.4 (D2)
PWR_EXT2: SV8.2, U$7.6 (D1)
PWR_EXT_CTRL1: U4.24 (PD4), U$9.5 (IN1)
PWR_EXT_CTRL2: SER_PWN_N_PD6.2, U4.25 (PD5)
RESET: R_PURESET.1, SV2.5, U4.35 (RESET!/PDI)
RX_EXT: R1.1, SV8.6
RX_EXT_PIN: R8.2, U4.32 (PE2)
SCL: R44.2, SV9.1, U4.29 (PE1)
SDA: R43.2, SV9.3, U4.28 (PE0)
SERVO1: R36.1, U4.41 (PA1)
SERVO2: R37.1, U4.42 (PA2)
SERVO3: R38.1, U4.43 (PA3)
SERVO4: R39.1, U4.44 (PA4)
SERVO_PWR_CTRL: SER_PWN_N_PD.2, SER_PWN_N_PD1.2, U4.3 (PA7)
SIG_CPU_BATT_CURRENT: U4.1 (PA5), U$17.7 (VIOUT)
SIG_MOTOR_CURRENT: U4.6 (PB2), U$12.7 (VIOUT)
TX_EXT: R40.2, SV8.5
TX_EXT_PIN: R2.1, U4.33 (PE3)

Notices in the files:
HW_RobotBoard2/RB1_v2.brd:
(c) Johannes, Sulkakoski, 2014, GPLv2
HW_RobotBoard4/RobotBoard4.brd:
(c) Johannes Sulkakoski, 2015, GPLv2
parts and their libraries:
SparkFun-Connectors: Licensing: CC v3.0 Share-Alike You are welcome to use this library for commercial purposes.
